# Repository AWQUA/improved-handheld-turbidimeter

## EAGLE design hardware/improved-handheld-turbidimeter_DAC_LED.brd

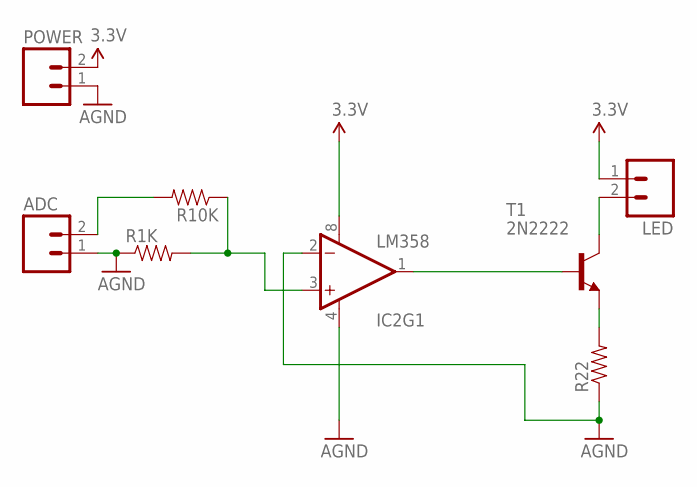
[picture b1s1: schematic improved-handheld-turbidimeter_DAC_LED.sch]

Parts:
ADC: M02PTH; 1X02
IC2: LM358; DIP08
LED: M02PTH; 1X02
POWER: M02PTH; 1X02
R1K, R10K, R22: RESISTOR0603-RES; 0603-RES
T1: 2N2222; TO92-EBC-OVAL

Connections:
3.3V: IC2.8 (V+), LED.1, POWER.2
AGND: ADC.1, IC2.2 (-IN), IC2.4 (V-), POWER.1, R1K.1, R22.1
unnamed: IC2.1 (OUT), T1.B
unnamed: LED.2, T1.C
unnamed: R22.2, T1.E
unnamed: ADC.2, R10K.2
unnamed: IC2.3 (+IN), R1K.2, R10K.1

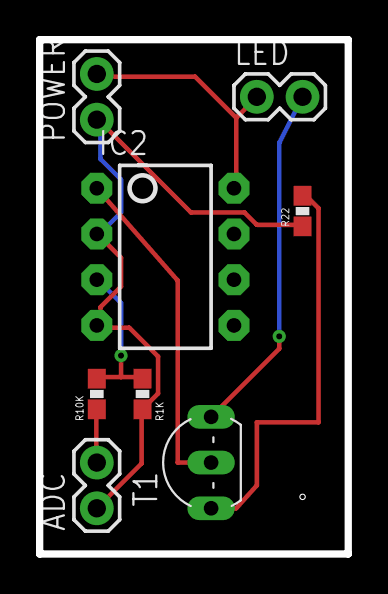
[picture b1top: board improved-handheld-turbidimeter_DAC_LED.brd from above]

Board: 2 copper layers, 17.1 x 28.6 mm, 8 parts (0 on the bottom side), 7 nets.

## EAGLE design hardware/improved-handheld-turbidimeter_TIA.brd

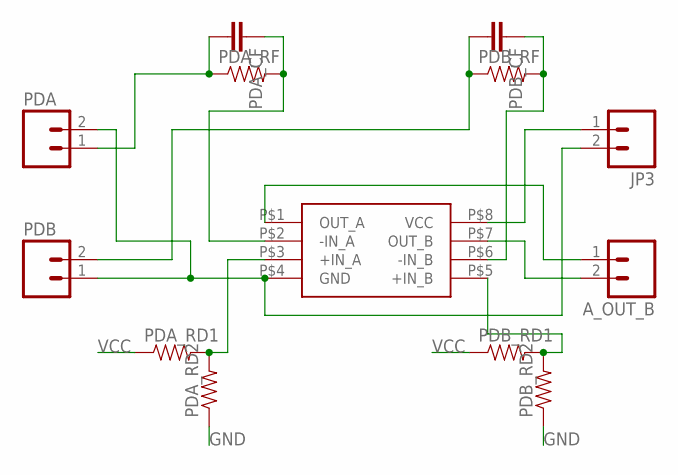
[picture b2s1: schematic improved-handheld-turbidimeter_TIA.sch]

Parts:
A_OUT_B: M02PTH; 1X02
JP3: M02PTH; 1X02
PDA: M02PTH; 1X02
PDA_CF: CAP0603-CAP; 0603-CAP
PDA_RD1, PDA_RD2: RESISTOR0603-RES; 0603-RES
PDA_RF: RESISTOR0603-RES; 0603-RES
PDB: M02PTH; 1X02
PDB_CF: CAP0603-CAP; 0603-CAP
PDB_RD1, PDB_RD2: RESISTOR0603-RES; 0603-RES
PDB_RF: RESISTOR0603-RES; 0603-RES
U$2: ADA4528-2

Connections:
GND: JP3.2, PDA.2, PDA_RD2.1, PDB.1, PDB_RD2.1, U$2.P$4 (GND)
unnamed: PDA.1, PDA_CF.2, PDA_RF.1
unnamed: PDA_CF.1, PDA_RF.2, U$2.P$2 (-IN_A)
unnamed: PDB.2, PDB_CF.2, PDB_RF.1
unnamed: PDB_CF.1, PDB_RF.2, U$2.P$6 (-IN_B)
unnamed: PDA_RD1.2, PDA_RD2.2, U$2.P$3 (+IN_A)
unnamed: PDB_RD1.2, PDB_RD2.2, U$2.P$5 (+IN_B)
OUTA: A_OUT_B.1, U$2.P$1 (OUT_A)
OUTB: A_OUT_B.2, U$2.P$7 (OUT_B)
VCC: JP3.1, PDA_RD1.1, PDB_RD1.1, U$2.P$8 (VCC)

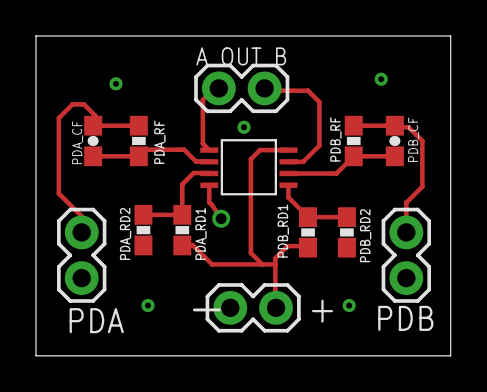
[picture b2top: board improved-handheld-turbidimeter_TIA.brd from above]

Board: 2 copper layers, 23.0 x 17.8 mm, 13 parts (0 on the bottom side), 10 nets.

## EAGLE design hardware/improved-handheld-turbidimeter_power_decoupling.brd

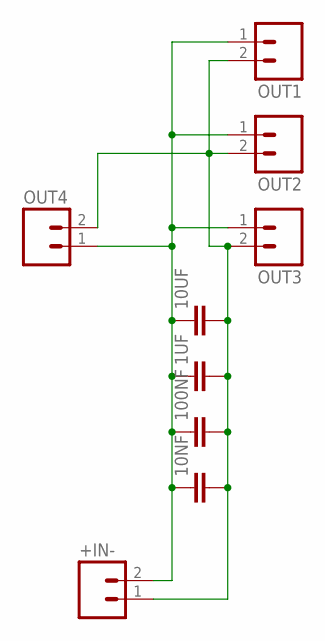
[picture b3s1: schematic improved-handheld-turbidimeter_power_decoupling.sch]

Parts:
1UF, 10NF, 10UF, 100NF: CAP0805; 0805
+IN-: M02PTH; 1X02
OUT1, OUT2, OUT3, OUT4: M02PTH; 1X02

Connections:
GND: 1UF.2, 10NF.2, 10UF.2, 100NF.2, +IN-.1, OUT1.2, OUT2.2, OUT3.2, OUT4.2
VCC: 1UF.1, 10NF.1, 10UF.1, 100NF.1, +IN-.2, OUT1.1, OUT2.1, OUT3.1, OUT4.1

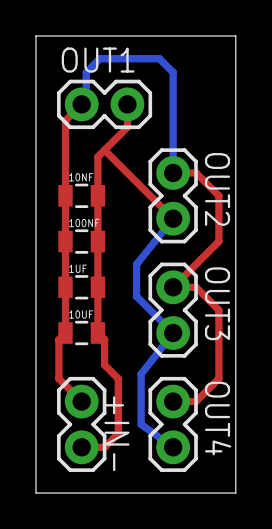
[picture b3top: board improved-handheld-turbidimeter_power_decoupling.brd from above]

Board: 2 copper layers, 11.1 x 25.4 mm, 9 parts (0 on the bottom side), 2 nets.

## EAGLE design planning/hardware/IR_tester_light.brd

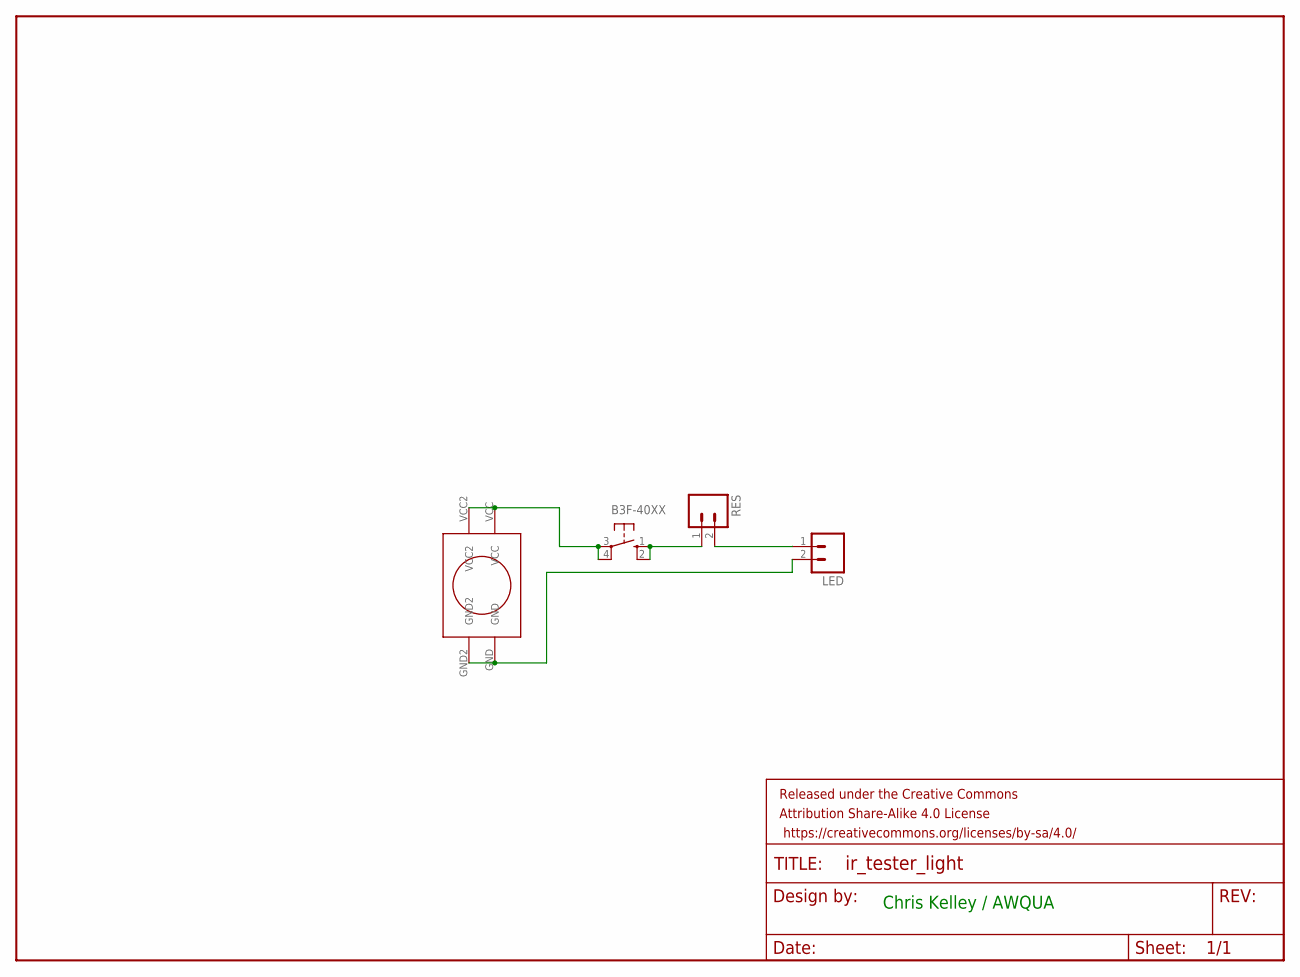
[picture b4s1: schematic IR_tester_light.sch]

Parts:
B3F-40XX: 40-XX; B3F-40XX
FRAME1: FRAME-LETTER; CREATIVE_COMMONS
LED: M02PTH; 1X02
RES: M02PTH; 1X02
U$1: CR1632-KEYSTYONE-3013

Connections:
GND: LED.2, U$1.GND, U$1.GND2
unnamed: LED.1, RES.2
unnamed: B3F-40XX.1 (S), B3F-40XX.2 (S1), RES.1
VCC: B3F-40XX.3, B3F-40XX.4 (P1), U$1.VCC, U$1.VCC2

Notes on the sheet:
Chris Kelley / AWQUA

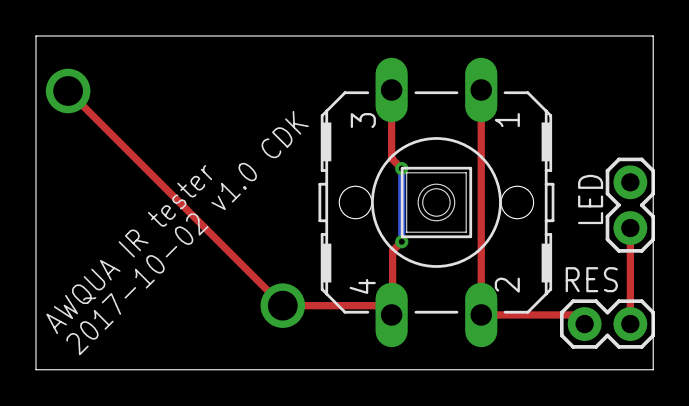
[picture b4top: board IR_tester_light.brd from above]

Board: 2 copper layers, 34.3 x 18.5 mm, 5 parts (1 on the bottom side), 4 nets.

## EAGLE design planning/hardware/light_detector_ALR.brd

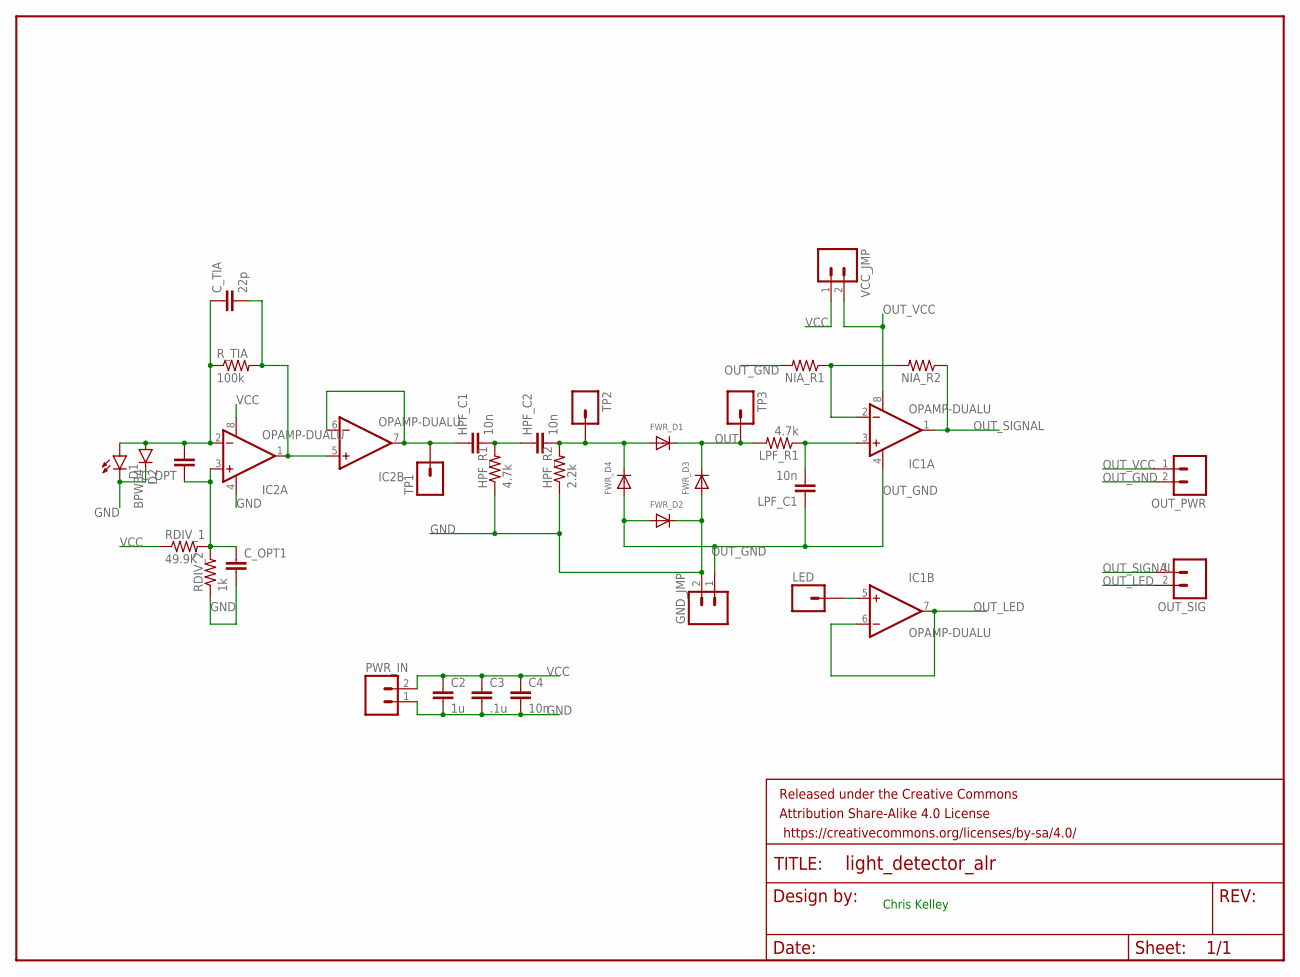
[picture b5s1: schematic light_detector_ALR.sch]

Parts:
C2: 1u; 0805
C3: .1u; 0805
C4: 10n; 0805
C_OPT, C_OPT1: CAP0805; 0805
C_TIA: 22p; 0805
D1: LED5MM
D2: BPW34
FRAME1: FRAME-LETTER; CREATIVE_COMMONS
FWR_D1, FWR_D2, FWR_D3, FWR_D4: DIODESOD-123; SOD-123
GND_JMP: M02PTH; 1X02
HPF_C1, HPF_C2: 10n; 0805
HPF_R1: 4.7k; 0603-RES
HPF_R2: 2.2k; 0603-RES
IC1, IC2: OPAMP-DUALU; SO08
LED: M01PTH; 1X01
LPF_C1: 10n; 0805
LPF_R1: 4.7k; 0603-RES
NIA_R1, NIA_R2: RESISTOR0603-RES; 0603-RES
OUT_PWR: M02PTH; 1X02
OUT_SIG: M02PTH; 1X02
PWR_IN: M02PTH; 1X02
RDIV_1: 49.9K; 0603-RES
RDIV_2: 1k; 0603-RES
R_TIA: 100k; 0603-RES
TP1, TP2, TP3: M01PTH; 1X01
VCC_JMP: M02PTH; 1X02

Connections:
GND: C2.2, C3.2, C4.2, C_OPT1.2, D1.K (C), D2.P$2 (C), FWR_D2.C, FWR_D3.A, GND_JMP.2, HPF_R1.1, HPF_R2.1, IC2.4 (V-), PWR_IN.1, RDIV_2.1
unnamed: C_OPT.2, C_TIA.1, D1.A, D2.P$1 (A), IC2.2 (-IN), R_TIA.1
unnamed: C_TIA.2, IC2.1 (OUT), IC2.5 (+IN), R_TIA.2
unnamed: C_OPT.1, C_OPT1.1, IC2.3 (+IN), RDIV_1.2, RDIV_2.2
unnamed: HPF_C1.2, HPF_C2.1, HPF_R1.2
unnamed: HPF_C1.1, IC2.6 (-IN), IC2.7 (OUT), TP1.1
unnamed: FWR_D1.A, FWR_D4.C, HPF_C2.2, HPF_R2.2, TP2.1
unnamed: IC1.3 (+IN), LPF_C1.2, LPF_R1.1
unnamed: IC1.2 (-IN), NIA_R1.1, NIA_R2.2
unnamed: IC1.5 (+IN), LED.1
OUT: FWR_D1.C, FWR_D3.C, LPF_R1.2, TP3.1
OUT_GND: FWR_D2.A, FWR_D4.A, GND_JMP.1, IC1.4 (V-), LPF_C1.1, NIA_R1.2, OUT_PWR.2
OUT_LED: IC1.6 (-IN), IC1.7 (OUT), OUT_SIG.2
OUT_SIGNAL: IC1.1 (OUT), NIA_R2.1, OUT_SIG.1
OUT_VCC: IC1.8 (V+), OUT_PWR.1, VCC_JMP.2
VCC: C2.1, C3.1, C4.1, IC2.8 (V+), PWR_IN.2, RDIV_1.1, VCC_JMP.1

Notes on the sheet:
Chris Kelley

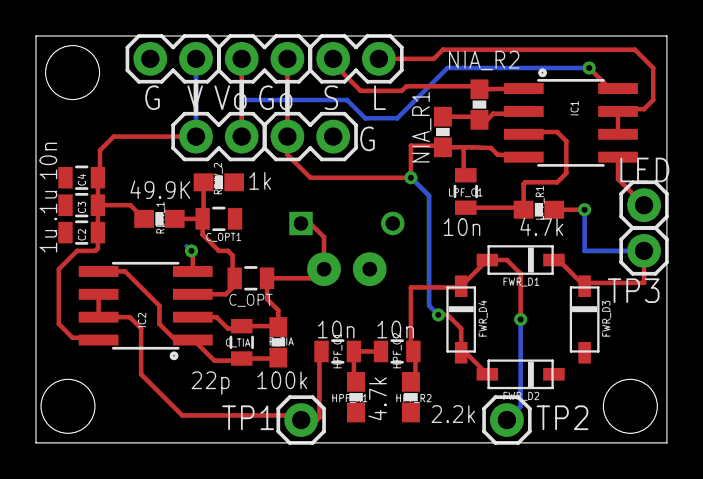
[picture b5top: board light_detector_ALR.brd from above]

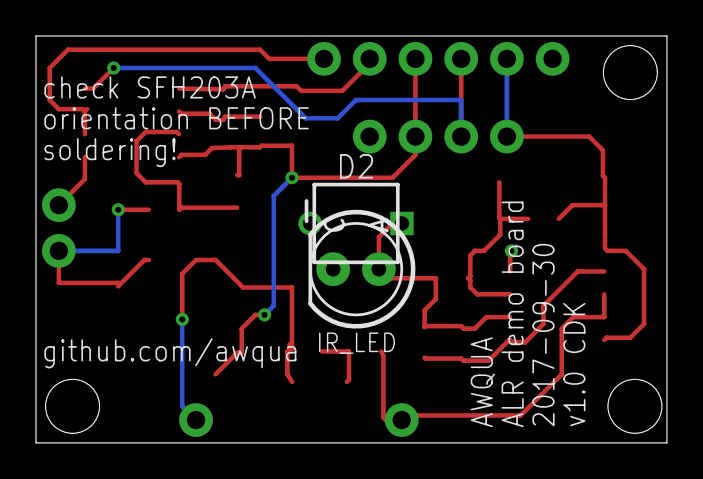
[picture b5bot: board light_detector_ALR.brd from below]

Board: 2 copper layers, 35.1 x 22.6 mm, 35 parts (2 on the bottom side), 16 nets.

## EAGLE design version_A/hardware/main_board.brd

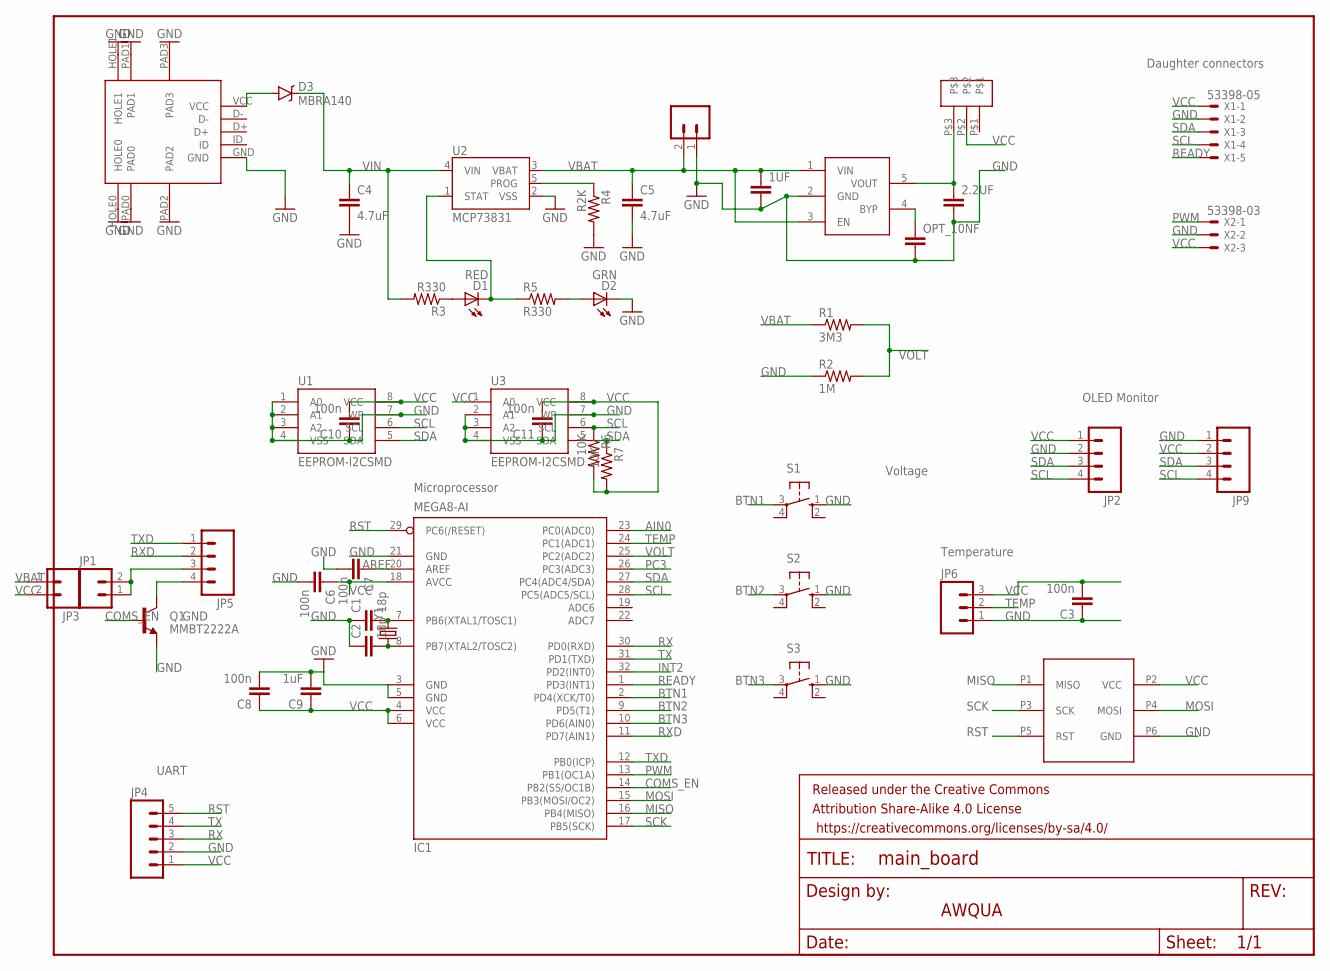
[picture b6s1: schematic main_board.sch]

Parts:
1UF, 2.2UF: CAP0603-CAP; 0603-CAP
C1, C2: 18p; 0603-CAP
C3, C6, C7, C8, C10, C11: 100n; 0603-CAP
C4, C5: 4.7uF; 0402-CAP
C9: 1uF; 0603-CAP
D1: RED; LED-0603
D2: GRN; LED-0603
D3: MBRA140; SMA-DIODE
FRAME1: FRAME-LETTER; CREATIVE_COMMONS
IC1: MEGA8-AI; TQFP32-08
JP1, JP3: M02PTH; 1X02
JP2, JP5, JP9: M04PTH; 1X04
JP4: M05PTH; 1X05
JP6: M03PTH; 1X03
JP7: LiPo Battery; JST-2-SMD
OPT_10NF: CAP0603-CAP; 0603-CAP
Q1: MMBT2222A; SOT23-3
R1: 3M3; 0603-RES
R2: 1M; 0603-RES
R3, R5: R330; 0402-RES
R4: R2K; 0402-RES
R6, R7: 10K; 0402-RES
S1, S2, S3: 40-XX; B3F-40XX
U1, U3: EEPROM-I2CSMD; SO08
U2: MCP73831; SOT23-5
U$1: ISP-SMD-6PIN
U$2: OS102-SPDT-SWITCH
U$3: USBMICRO-10118193-0001LF
U$6: LP2985
X1: 53398-05
X2: 53398-03
Y1: CRYSTAL5X3; CRYSTAL-SMD-5X3

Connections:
AIN0: IC1.23 (PC0(ADC0))
AREF: C7.1, IC1.20 (AREF)
BTN1: IC1.2 (PD4(XCK/T0)), S1.3
BTN2: IC1.9 (PD5(T1)), S2.3
BTN3: IC1.10 (PD6(AIN0)), S3.3
COMS_EN: IC1.14 (PB2(SS/OC1B)), Q1.1 (B)
GND: 1UF.2, 2.2UF.2, C1.1, C2.1, C3.1, C4.2, C5.2, C6.2, C7.2, C8.2, C9.2, C10.1, C11.1, D2.C, IC1.3 (GND), IC1.5 (GND), IC1.21 (GND), JP2.2, JP4.2, JP5.4, JP6.1, JP7.1, JP9.1, OPT_10NF.2, Q1.2 (E), Q1.3 (C), R2.1, R4.2, S1.1 (S), S2.1 (S), S3.1 (S), U1.1 (A0), U1.2 (A1), U1.3 (A2), U1.4 (VSS), U1.7 (WP), U2.2 (VSS), U3.2 (A1), U3.3 (A2), U3.4 (VSS), U3.7 (WP), U$1.P6 (GND), U$3.GND, U$3.HOLE0, U$3.HOLE1, U$3.PAD0, U$3.PAD1, U$3.PAD2, U$3.PAD3, U$6.2 (GND), X1.2, X2.2
INT2: IC1.32 (PD2(INT0))
MISO: IC1.16 (PB4(MISO)), U$1.P1 (MISO)
MOSI: IC1.15 (PB3(MOSI/OC2)), U$1.P4 (MOSI)
unnamed: D1.A, R3.1
unnamed: OPT_10NF.1, U$6.4 (BYP)
unnamed: JP1.1, JP1.2, JP5.3
unnamed: 2.2UF.1, U$2.P$3, U$6.5 (VOUT)
unnamed: D2.A, R5.2
PC3: IC1.26 (PC3(ADC3))
PROG: R4.1, U2.5 (PROG)
PWM: IC1.13 (PB1(OC1A)), X2.1
Q1: C2.2, IC1.8 (PB7(XTAL2/TOSC2)), Y1.1
Q2: C1.2, IC1.7 (PB6(XTAL1/TOSC1)), Y1.3 (2)
READY: IC1.1 (PD3(INT1)), X1.5
RST: IC1.29 (PC6(/RESET)), JP4.5, U$1.P5 (RST)
RX: IC1.30 (PD0(RXD)), JP4.3
RXD: IC1.11 (PD7(AIN1)), JP5.2
SCK: IC1.17 (PB5(SCK)), U$1.P3 (SCK)
SCL: IC1.28 (PC5(ADC5/SCL)), JP2.4, JP9.4, R6.1, U1.6 (SCL), U3.6 (SCL), X1.4
SDA: IC1.27 (PC4(ADC4/SDA)), JP2.3, JP9.3, R7.1, U1.5 (SDA), U3.5 (SDA), X1.3
STAT: D1.C, R5.1, U2.1 (STAT)
TEMP: IC1.24 (PC1(ADC1)), JP6.2
TX: IC1.31 (PD1(TXD)), JP4.4
TXD: IC1.12 (PB0(ICP)), JP5.1
VBAT: 1UF.1, C5.1, JP3.1, JP7.2, R1.1, U2.3 (VBAT), U$6.1 (VIN), U$6.3 (EN)
VBUS: D3.A, U$3.VCC
VCC: C3.2, C6.1, C8.1, C9.1, C10.2, C11.2, IC1.4 (VCC), IC1.6 (VCC), IC1.18 (AVCC), JP2.1, JP3.2, JP4.1, JP6.3, JP9.2, R6.2, R7.2, U1.8 (VCC), U3.1 (A0), U3.8 (VCC), U$1.P2 (VCC), U$2.P$2, X1.1, X2.3
VIN: C4.1, D3.C, R3.2, U2.4 (VIN)
VOLT: IC1.25 (PC2(ADC2)), R1.2, R2.2

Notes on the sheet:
AWQUA
Temperature
Voltage
UART
Microprocessor
OLED Monitor
Daughter connectors

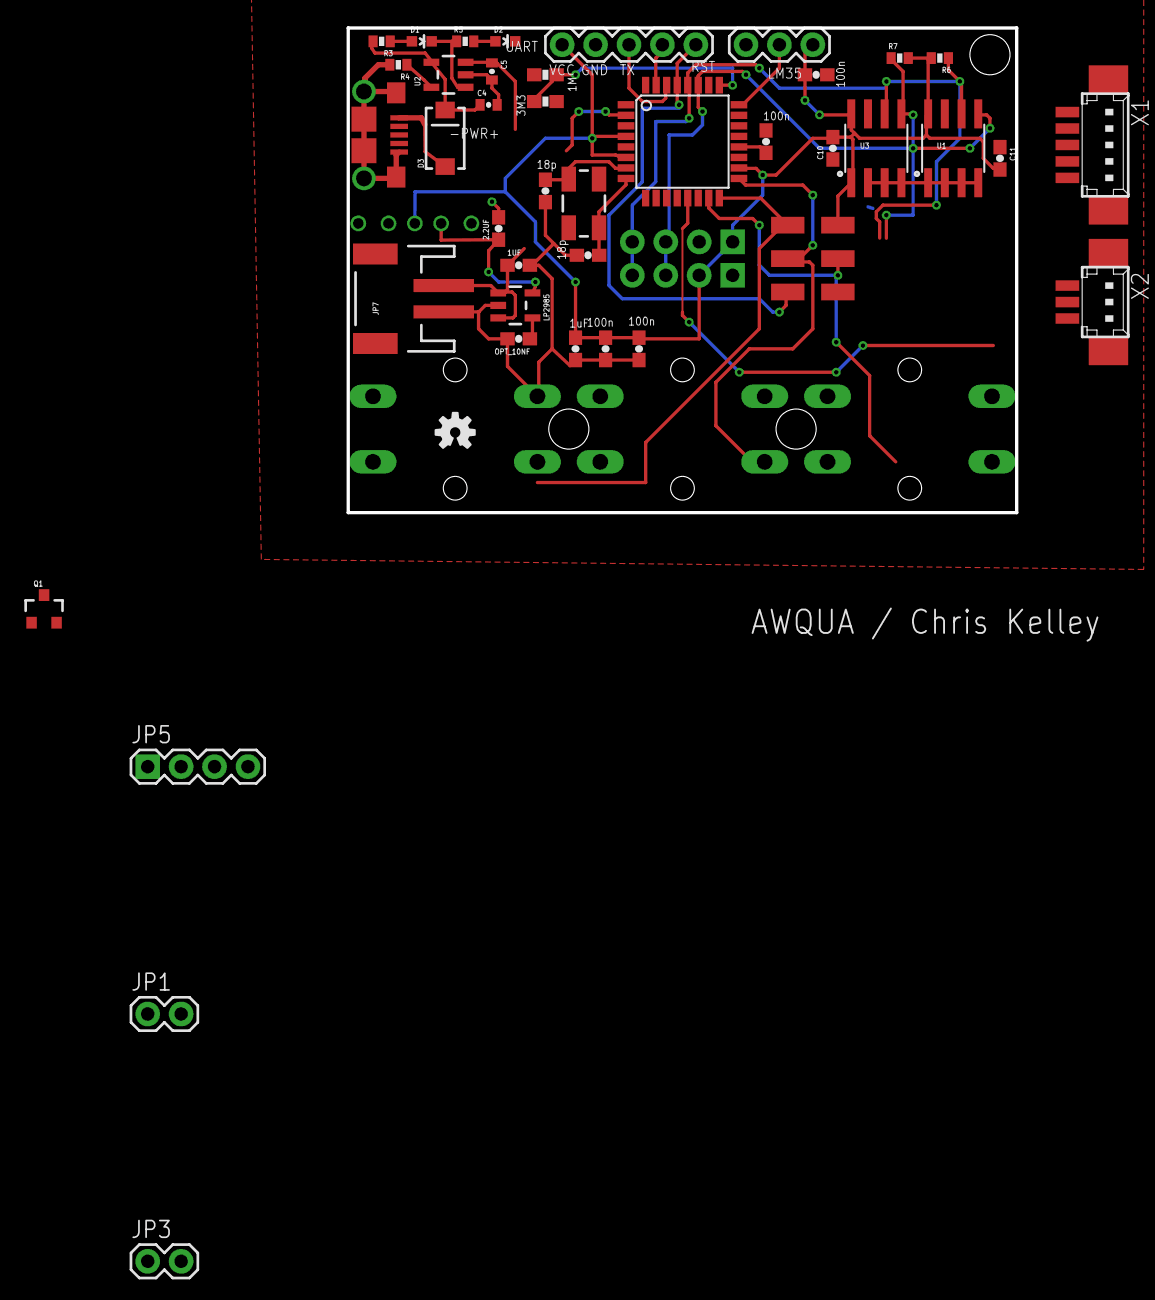
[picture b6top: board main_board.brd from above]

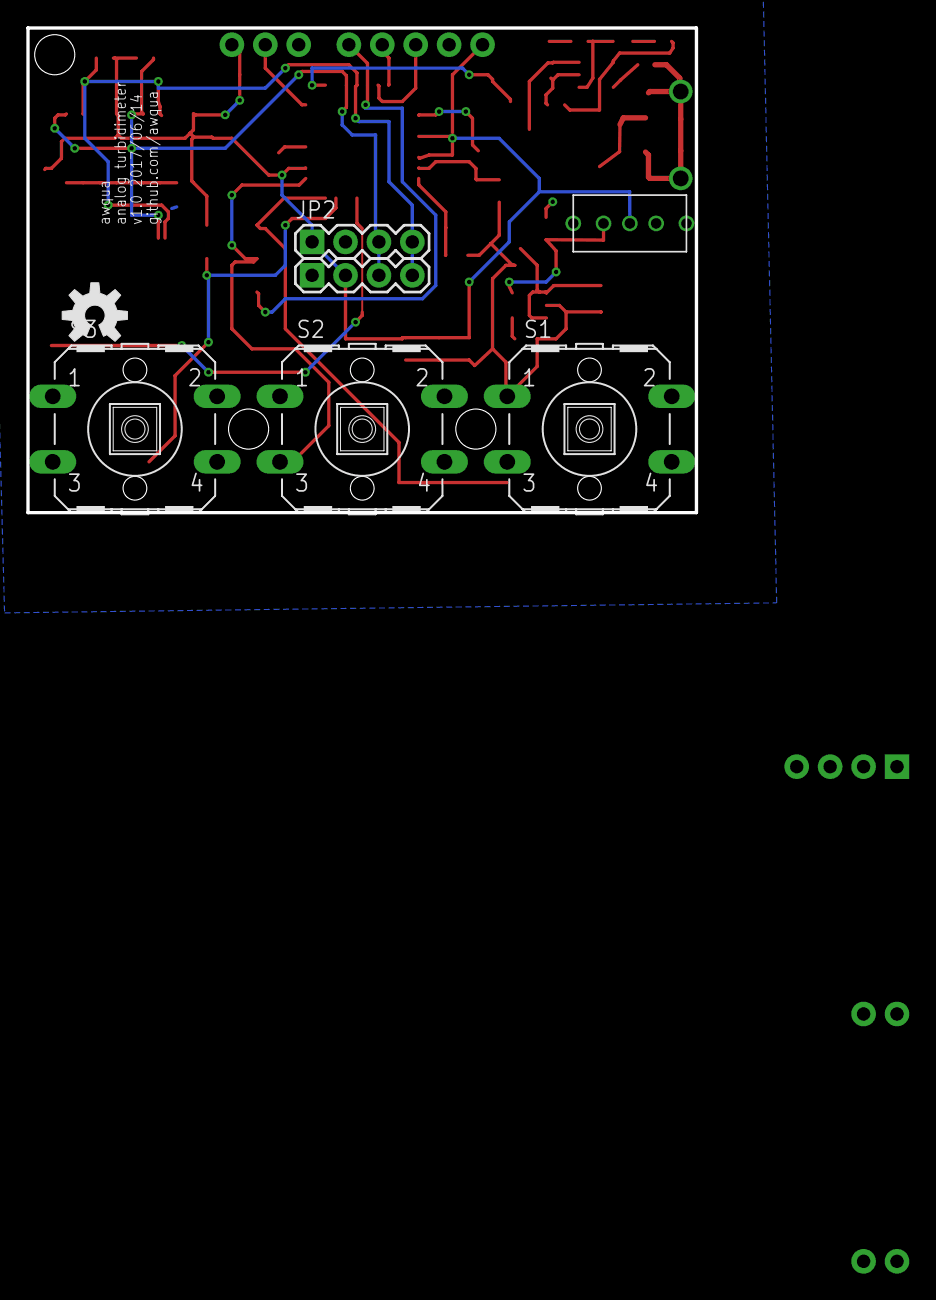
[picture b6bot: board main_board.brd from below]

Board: 2 copper layers, 50.8 x 36.8 mm, 50 parts (7 on the bottom side), 33 nets.

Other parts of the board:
U$4: OSHW-LOGO-M
U$5: OSHW-LOGO-S

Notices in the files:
parts and their libraries:
SparkFun-AnalogIC: Licensing:Creative Commons ShareAlike 4.0 International - https://creativecommons.org/licenses/by-sa/4.0
SparkFun-Aesthetics: Released under the Creative Commons Attribution Share-Alike 4.0 License
SparkFun-Aesthetics: https://creativecommons.org/licenses/by-sa/4.0
